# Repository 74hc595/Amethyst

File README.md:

# The Amethyst Colour Video System

https://www.youtube.com/watch?v=6GKgxBEGH1M

The Amethyst is a retro-styled "home computer" built around an Atmel ATmega1284 microcontroller.
It features composite (NTSC) video output with both high-color and high-resolution modes, mono
audio output, and a full-travel mechanical keyboard. It includes a full-featured implementation
of the powerful Forth programming language, with graphics and sound commands, debugger, and
screen editor. A single USB Type-B cable provides 5V power as well as serial communication with
a PC. Amethyst is compatible with the Optiboot (Arduino) bootloader, and new firmware may be
uploaded to it without a specialized programming device.

## Full specifications

- ATmega1284 microcontroller (8-bit) running at 14.318 MHz
- 16KB internal memory (16352 bytes available for applications)
- 4KB nonvolatile EEPROM memory
- Mechanical keyboard with Cherry MX keyswitches
- NTSC color and monochrome composite video output:

    - 256-color, 16-color, and 4-color bitmap graphics at resolutions up to 160x200 pixels
    - Monochrome bitmap graphics at resolutions up to 640x200 pixels
    - 40x25 and 80x25 monochrome text modes
    - 40x25 color text mode
    - 40x25 color tiled graphics modes
    
- Single-channel audio output (pulse wave or PWM)
- USB serial communication at speeds up to 57600 baud
- Four SPI expansion ports for peripherals, controllers, and storage devices
- Only 6 chips (ATmega1284, FT320X, 2x 74HC157, 2x 74HC166)

**TODO 1/5/20: add more detailed docs, instructions, and BOM**

## About

Amethyst is a hobby project and is not currently available for purchase in kit or built form.

Copyright 2019 Matt Sarnoff.

https://twitter.com/txsector

http://msarnoff.org

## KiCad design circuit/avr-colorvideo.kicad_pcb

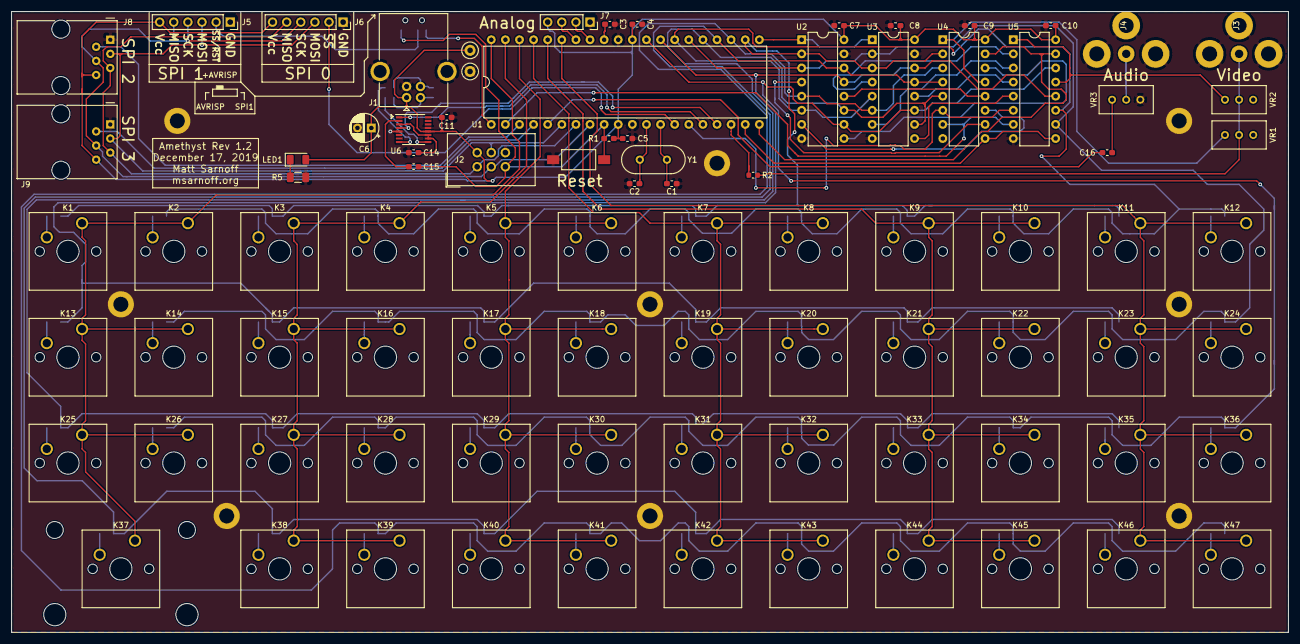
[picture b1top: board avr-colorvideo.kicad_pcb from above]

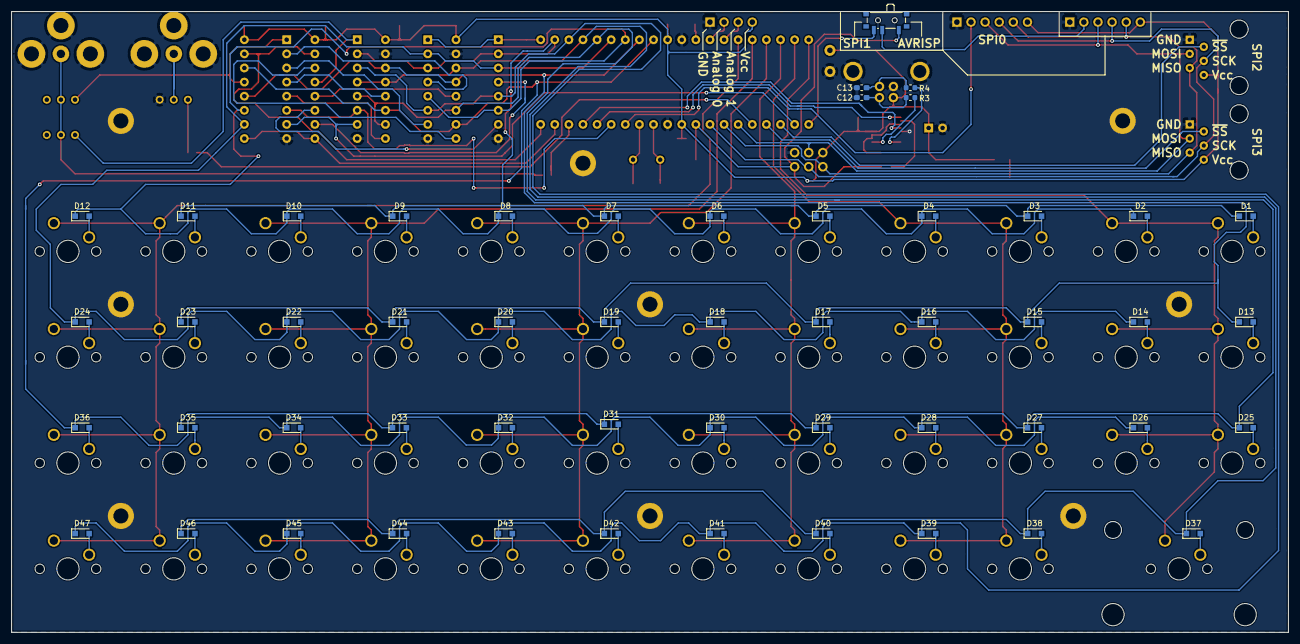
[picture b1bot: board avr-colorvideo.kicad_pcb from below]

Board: 2 copper layers, 229.9 x 111.8 mm, 139 parts (52 on the bottom side), 106 nets.

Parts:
C1, C2: 18pF; C_0603_1608Metric_Pad1.05x0.95mm_HandSolder
C3, C4, C5, C7, C8, C9, C10, C11, C14, C15, C16: 0.1uF; C_0603_1608Metric_Pad1.05x0.95mm_HandSolder
C6: 10uF; CP_Radial_D5.0mm_P2.50mm
C12, C13: 47pF; C_0603_1608Metric_Pad1.05x0.95mm_HandSolder
D1, D2, D3, D4, D5, D6, D7, D8, D9, D10, D11, D12, D13, D14, D15, D16, D17, D18, D19, D20, D21, D22, D23, D24, D25, D26, D27, D28, D29, D30, D31, D32, D33, D34, D35, D36, D37, D38, D39, D40, D41, D42, D43, D44, D45, D46, D47: D_Small; D_SOD-323_HandSoldering
J1: USB-B; USB_B_OST_USB-B1HSxx_Horizontal
J2: AVR-ISP-6; IDC-Header_2x03_P2.54mm_Vertical
J3, J4: RCA; RCA_Jack_Jameco_KY-006-1
J5: SPI1; PinSocket_1x06_P2.54mm_Vertical
J6: SPI0; PinSocket_1x06_P2.54mm_Vertical
J7: ANALOG; PinSocket_1x04_P2.54mm_Vertical
J8, J9: 6P6C; RJ12_Amphenol_54601
K1, K2, K3, K4, K5, K6, K7, K8, K9, K10, K11, K12, K13, K14, K15, K16, K17, K18, K19, K20, K21, K22, K23, K24, K25, K26, K27, K28, K29, K30, K31, K32, K33, K34, K35, K36, K38, K39, K40, K41, K42, K43: SW_Push; SW_Cherry_MX1A_1.00u_PCB
K37: SW_Push; SW_Cherry_MX_2.00u_PCB
K44, K45, K46, K47: SW_Push; SW_Cherry_MX_1.00u_PCB
LED1: LED_Small; LED_1206_3216Metric
R1: 10k; R_0603_1608Metric_Pad1.05x0.95mm_HandSolder
R2: 1k; R_0603_1608Metric
R3, R4: 27; R_0603_1608Metric
R5: 1.5k; R_1206_3216Metric
SW1: SW_Push; SW_SPST_FSMSM
SW2: SPI1/ISP; SW_SPDT_PCM12
TP1, TP2: TestPoint; TestPoint_Loop_D1.80mm_Drill1.0mm_Beaded
U1: ATmega1284P-PU; DIP-40_W15.24mm
U2, U3: 74HC157; DIP-16_W7.62mm
U4, U5: 74HC166; DIP-16_W7.62mm
U6: FT230XS; SSOP-16_3.9x4.9mm_P0.635mm
VR1, VR2: 2k; Potentiometer_Bourns_3296W_Vertical
VR3: 10k; Potentiometer_Bourns_3296W_Vertical
Y1: 14.31818MHz; Crystal_HC49-4H_Vertical

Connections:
/ANA0: J7.2, U1.33
/ANA1: J7.3, U1.34
/AREF: C3.1, U1.32
/AUDIO: C16.2, U1.5
/KR0: K1.1, K2.1, K13.1, K14.1, K25.1, K26.1, K37.1, U1.40
/KR1: K3.1, K4.1, K15.1, K16.1, K27.1, K28.1, K38.1, K39.1, U1.39
/KR2: K5.1, K6.1, K17.1, K18.1, K29.1, K30.1, K40.1, K41.1, U1.38
/KR3: K7.1, K8.1, K19.1, K20.1, K31.1, K32.1, K42.1, K43.1, U1.37
/KR4: K9.1, K10.1, K21.1, K22.1, K33.1, K34.1, K44.1, K45.1, U1.36
/KR5: K11.1, K12.1, K23.1, K24.1, K35.1, K36.1, K46.1, K47.1, U1.35
/MISO: J2.1, J5.5, J6.5, J8.5, J9.5, U1.7
/MOSI: J2.4, J5.3, J6.3, J8.3, J9.3, U1.6
/PC0: D1.1, D3.1, D5.1, D7.1, D9.1, D11.1, U1.22, U2.2, U3.3, U4.2
/PC1: D39.1, D41.1, D43.1, D45.1, D47.1, U1.23, U2.5, U3.6, U4.3
/PC2: D37.1, D38.1, D40.1, D42.1, D44.1, D46.1, U1.24, U2.14, U3.13, U4.4
/PC3: D25.1, D27.1, D29.1, D31.1, D33.1, D35.1, U1.25, U2.11, U3.10, U4.5
/PC4: D14.1, D16.1, D18.1, D20.1, D22.1, D24.1, U1.26, U2.3, U3.2, U5.10
/PC5: D2.1, D4.1, D6.1, D8.1, D10.1, D12.1, U1.27, U2.6, U3.5, U5.11
/PC6: D13.1, D15.1, D17.1, D19.1, D21.1, D23.1, U1.28, U2.13, U3.14, U5.12
/PC7: D26.1, D28.1, D30.1, D32.1, D34.1, D36.1, U1.29, U2.10, U3.11, U5.14
/PXCLK: U1.2, U4.7, U5.7
/RX: U1.16, U6.1
/SCK: J2.3, J5.4, J6.4, J8.4, J9.4, U1.8
/SRMODE: U1.21, U2.1, U3.1
/TX: U1.17, U6.4
/USBDM: C12.1, J1.2, R3.2
/USBDP: C13.1, J1.3, R4.2
/~BLANK: U1.19, U4.9, U5.9
/~RESET: C15.1, J2.5, R1.1, SW1.2, SW2.1, U1.9
/~SHIFTEN: U1.15, U4.6, U5.6
/~SRLOAD: U1.20, U4.15, U5.15
/~SS0: J6.2, U1.14
/~SS1: SW2.3, U1.1
/~SS2: J8.2, U1.3
/~SS3: J9.2, U1.4
/~SYNC: R2.2, U1.18
GND: C1.2, C2.2, C3.2, C4.2, C5.1, C6.2, C7.2, C8.2, C9.2, C10.2, C11.2, C12.2, C13.2, C14.2, J1.4, J1.5, J2.6, J3.2, J4.2, J5.1, J6.1, J7.1, J8.1, J9.1, R5.1, SW1.1, TP2.1, U1.11, U1.31, U2.8, U2.15, U3.8, U3.15, U4.8, U5.8, U6.5, U6.13, VR3.3
unnamed: C1.1, U1.13, Y1.2
unnamed: C2.1, U1.12, Y1.1
unnamed: C14.1, U6.3, U6.10, U6.11
unnamed: C15.2, U6.2
unnamed: C16.1, VR3.1
unnamed: D1.2, K1.2
unnamed: D2.2, K2.2
unnamed: D3.2, K3.2
unnamed: D4.2, K4.2
unnamed: D5.2, K5.2
unnamed: D6.2, K6.2
unnamed: D7.2, K7.2
unnamed: D8.2, K8.2
unnamed: D9.2, K9.2
unnamed: D10.2, K10.2
unnamed: D11.2, K11.2
unnamed: D12.2, K12.2
unnamed: D13.2, K13.2
unnamed: D14.2, K14.2
unnamed: D15.2, K15.2
unnamed: D16.2, K16.2
unnamed: D17.2, K17.2
unnamed: D18.2, K18.2
unnamed: D19.2, K19.2
unnamed: D20.2, K20.2
unnamed: D21.2, K21.2
unnamed: D22.2, K22.2
unnamed: D23.2, K23.2
unnamed: D24.2, K24.2
unnamed: D25.2, K25.2
unnamed: D26.2, K26.2
unnamed: D27.2, K27.2
unnamed: D28.2, K28.2
unnamed: D29.2, K29.2
unnamed: D30.2, K30.2
unnamed: D31.2, K31.2
unnamed: D32.2, K32.2
unnamed: D33.2, K33.2
unnamed: D34.2, K34.2
unnamed: D35.2, K35.2
unnamed: D36.2, K36.2
unnamed: D37.2, K37.2
unnamed: D38.2, K38.2
unnamed: D39.2, K39.2
unnamed: D40.2, K40.2
unnamed: D41.2, K41.2
unnamed: D42.2, K42.2
unnamed: D43.2, K43.2
unnamed: D44.2, K44.2
unnamed: D45.2, K45.2
unnamed: D46.2, K46.2
unnamed: D47.2, K47.2
unnamed: J3.1, R2.1, VR1.2, VR2.2
unnamed: J4.1, VR3.2
unnamed: J5.2, SW2.2
unnamed: LED1.1, R5.2
unnamed: R3.1, U6.9
unnamed: R4.1, U6.8
unnamed: U2.4, U4.10
unnamed: U2.7, U4.11
unnamed: U2.9, U4.14
unnamed: U2.12, U4.12
unnamed: U3.4, U5.2
unnamed: U3.7, U5.3
unnamed: U3.9, U5.5
unnamed: U3.12, U5.4
unnamed: U4.1, U4.13, VR1.1
unnamed: U5.1, U5.13, VR2.1
VCC: C4.1, C5.2, C6.1, C7.1, C8.1, C9.1, C10.1, C11.1, J1.1, J2.2, J5.6, J6.6, J7.4, J8.6, J9.6, LED1.2, R1.2, TP1.1, U1.10, U1.30, U2.16, U3.16, U4.16, U5.16, U6.12

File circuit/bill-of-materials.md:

## Amethyst Bill of Materials

| Reference              | Qty | Description                                               | Vendor link |
| ---------------------- | --- | --------------------------------------------------------- | ----------- |
| C1-C2                  | 2   | Capacitor, MLCC, 0603, 18pF, 50V, NPO, 5%                 | [Mouser](https://www.mouser.com/ProductDetail/603-CC603JRNPO9BN180) |
| C3-C5, C7-C11, C14-C16 | 10  | Capacitor, MLCC, 0603, 0.1uF, 10V, X7R, 5%                | [Mouser](https://www.mouser.com/ProductDetail/77-VJ0603Y104JXQCBC) |
| C6                     | 1   | Capacitor, electrolytic, through-hole, 10uF, 25V          | Generic [(Amazon)](https://www.amazon.com/REXQualis-Electrolytic-Capacitor-Asso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 |
| C12-C13                | 2   | Capacitor, MLCC, 0603, 47pF, 100V, C0G, 5%                | [Mouser](https://www.mouser.com/ProductDetail/KEMET/C0603C470J1GACTU?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 |
| D1-D47                 | 47  | Diode, SMD, BAS16HT1G                                     | [Mouser](https://www.mouser.com/ProductDetail/863-BAS16HT1G) |
| J1                     | 1   | Connector, USB-B, right-angle, through-hole               | [Jameco](https://www.jameco.com/shop/ProductDisplay?catalogId=10001&l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 |
| J2                     | 1   | Pin header, 0.1" pitch, straight, through hole, 2x3       | Generic [(Amazon)](https://www.amazon.com/Frienda-Break-Away-Connector-Compatib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 |
| J3                     | 1   | Connector, RCA, female, right-angle, through-hole, yellow | [Jameco](https://www.jameco.com/z/KY-006-1-Y--Connector-RCA-Female-2-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 |
| J4                     | 1   | Connector, RCA, female, right-angle, through-hole, white  | [Jameco](https://www.jameco.com/z/KY-006-1-Y--Connector-RCA-Female-2-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 |
| J5-J6                  | 2   | Pin socket, 0.1" pitch, right-angle, through-hole, 1x6    | Generic [(Amazon)](https://www.amazon.com/Right-Female-Header-2-54mm-Connector/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 |
| J7                     | 1   | Pin socket, 0.1" pitch, right-angle, through-hole, 1x4    | Generic [(Amazon)](https://www.amazon.com/Right-Female-Header-2-54mm-Connector/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 |
| J8-J9                  | 2   | Connector, RJ-11, right-angle, through-hole, 6P6C         | [Amazon](https://www.amazon.com/gp/product/B00LUT5VA4/ref=ppx_yo_dt_b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 |
| K1-K47                 | 47  | Keyswitch, Cherry MX, PCB mount (any color)               | [MechanicalKeyboards.com](https://mechanicalkeyboards.com/shop/index.php?l=product_det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 |
| (K1-K47)               | 1   | DSA "Beyond" keycap set                                   | [PimpMyKeyboard.com](https://pimpmykeyboard.com/dsa-beyond-keyset-sublimated/) |
| LED1                   | 1   | LED, SMD, 1206 (any color)                                | Generic [(Amazon)](https://www.amazon.com/Assorted-Lighting-Electronics-Compone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 |
| R1                     | 1   | Resistor, SMD, 0603, 10k ohm, 100 mW, 5%                  | [Mouser](https://www.mouser.com/ProductDetail/Yageo/RC0603JR-0710KL?q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 |
| R2                     | 1   | Resistor, SMD, 0603, 1k ohm, 100 mW, 5%                   | [Mouser](https://www.mouser.com/ProductDetail/Yageo/RC0603JR-071KL?qs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 |
| R3-R4                  | 2   | Resistor, SMD, 0603, 27 ohm, 100 mW, 1%                   | [Mouser](https://www.mouser.com/ProductDetail/Yageo/RC0603FR-0727RL?q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 |
| R5                     | 1   | Resistor, SMD, 1206, 1.5k ohm*, 1/4 W, 1%                 | [Mouser](https://www.mouser.com/ProductDetail/Yageo/RT1206FRE071K5L?q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 |
| SW1                    | 1   | Push switch, FSMSM                                        | [Mouser](https://www.mouser.com/ProductDetail/TE-Connectivity-Alcoswi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 |
| SW2                    | 1   | Slide switch, SMD, PCM12                                  | [Amazon](https://www.amazon.com/gp/product/B01GFFGA4I/ref=ppx_yo_dt_b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, [Mouser](https://www.mouser.com/ProductDetail/CK/PCM12SMTR?qs=mfFuHy8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 |
| U1                     | 1   | IC, ATmega1284P-PU, DIP-40                                | [Mouser](https://www.mouser.com/ProductDetail/Microchip-Technology-At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 |
| (U1)                   | 1   | IC socket, 40 pin DIP                                     | Generic [(Amazon)](https://www.amazon.com/Glarks-122Pcs-adaptadores-soldadura-4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 |
| U2-U3                  | 2   | IC, 74HC157, DIP-16                                       | [Mouser](https://www.mouser.com/ProductDetail/Texas-Instruments/SN74H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 |
| U4-U5                  | 2   | IC, 74HC166, DIP-16                                       | [Mouser](https://www.mouser.com/ProductDetail/595-SN74HC166N) |
| (U2-U5)                | 4   | IC socket, 16 pin DIP                                     | Generic [(Amazon)](https://www.amazon.com/Glarks-122Pcs-adaptadores-soldadura-4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 |
| U6                     | 1   | IC, FT230XS-R, SSOP-16                                    | [Mouser](https://www.mouser.com/ProductDetail/895-FT230XS-R) |
| VR1-VR2                | 2   | Potentiometer, 2k ohm, Bourns 3296W (or clone)            | [Amazon](https://www.amazon.com/gp/product/B0711MB4TL/ref=ppx_yo_dt_b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 |
| VR3                    | 1   | Potentiometer, 10k ohm, Bourns 3296W (or clone)           | [Amazon](https://www.amazon.com/gp/product/B0711MB4TL/ref=ppx_yo_dt_b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 |
| Y1                     | 1   | Crystal, HC-49/US, 14.31818MHz                            | [Mouser](https://www.mouser.com/ProductDetail/ABRACON/ABL-1431818MHZ-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 |
| PCB                    | 1   | Amethyst printed circuit board, rev 1.2                   | [OSHPark](https://oshpark.com/shared_projects/2bLMCsl2), [JLCPCB](https://cart.jlcpcb.com/quote?uploadNum=9795c353e69442e1ac3e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 |

_*_ R5: actual value will depend on color of LED1 and desired brightness.

You will also need an AVR programmer to burn the bootloader to the ATmega1284P (U1). The [AVRISP mkII](https://www.microchip.com/DevelopmentTools/ProductDetails/Pa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 is no longer manufatured,
but there are other options:

- [SparkFun Pocket AVR Programmer](https://www.sparkfun.com/products/9825)
- An [Arduino](https://www.arduino.cc/en/Tutorial/ArduinoISP) can be used as an ISP programmer
- [SparkFun AVR Programmer HAT](https://www.sparkfun.com/products/14747) for Raspberry Pi
- [AVRISP mkII clones](https://www.amazon.com/official-Programmer-Compatible-Suppor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 are available

Note that I have only tested burning the bootloader with an official AVRISP mkII unit, and I can't
provide specific instructions for these alternatives at this time.

Once the bootloader has been burned to the ATmega chip, the AVR programmer is no longer required.
Further programming only requires a USB-B cable.

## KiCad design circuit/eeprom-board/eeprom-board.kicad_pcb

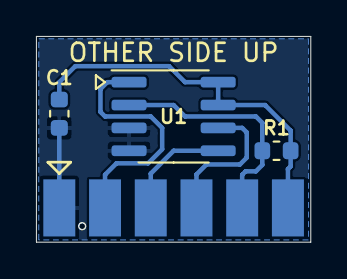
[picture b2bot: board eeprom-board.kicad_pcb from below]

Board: 2 copper layers, 15.2 x 11.4 mm, 4 parts (4 on the bottom side), 6 nets.

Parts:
C1: 0.1uF; C_0603_1608Metric
J1: Conn_01x06; Conn_1x06_P2.54mm_Horizontal_SMD
R1: 1k; R_0603_1608Metric
U1: CAT250xxx; SOIC-8_3.9x4.9mm_P1.27mm

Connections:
/MISO: J1.5, R1.2, U1.2
/MOSI: J1.3, U1.5
/SCK: J1.4, U1.6
/~SS: J1.2, U1.1
GND: C1.2, J1.1, U1.3, U1.4
VCC: C1.1, J1.6, R1.1, U1.7, U1.8

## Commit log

2020-01-01 Create LICENSE
2020-01-06 add prebuilt bootloader hex and enlosure svgs
2020-01-06 update readme todo
2020-07-10 [#2] add schematic pdf
2020-07-10 fixes #2 - add image of board layers
2020-07-25 add bill of materials
